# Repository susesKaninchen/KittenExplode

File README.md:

# KittenExplode
Das Projekt besteht aus einem I2C MAster und einer Reihe von I2C Slaves.

Momentan ist es auf ESP32 ausgelegt, diese haben kein I2C stretching und deswegen verhalten sie sich anders als ESP32 C3 oder STM32 oder Arduinos. Der Slave code müste dann angepasst werden.

Der Slave kann das Status Byte (statusChar) anpassen um dem Master bescheid zu geben wie der aktuelle Status ist.
Der Master kann das EndByte (endByte) anpassen um den Slaves den Stand des Spiel mitzuteilen.
Der vom Master gesetzte Seed (seed) soll genutzt werden um die Slaves zu konfigurieren.

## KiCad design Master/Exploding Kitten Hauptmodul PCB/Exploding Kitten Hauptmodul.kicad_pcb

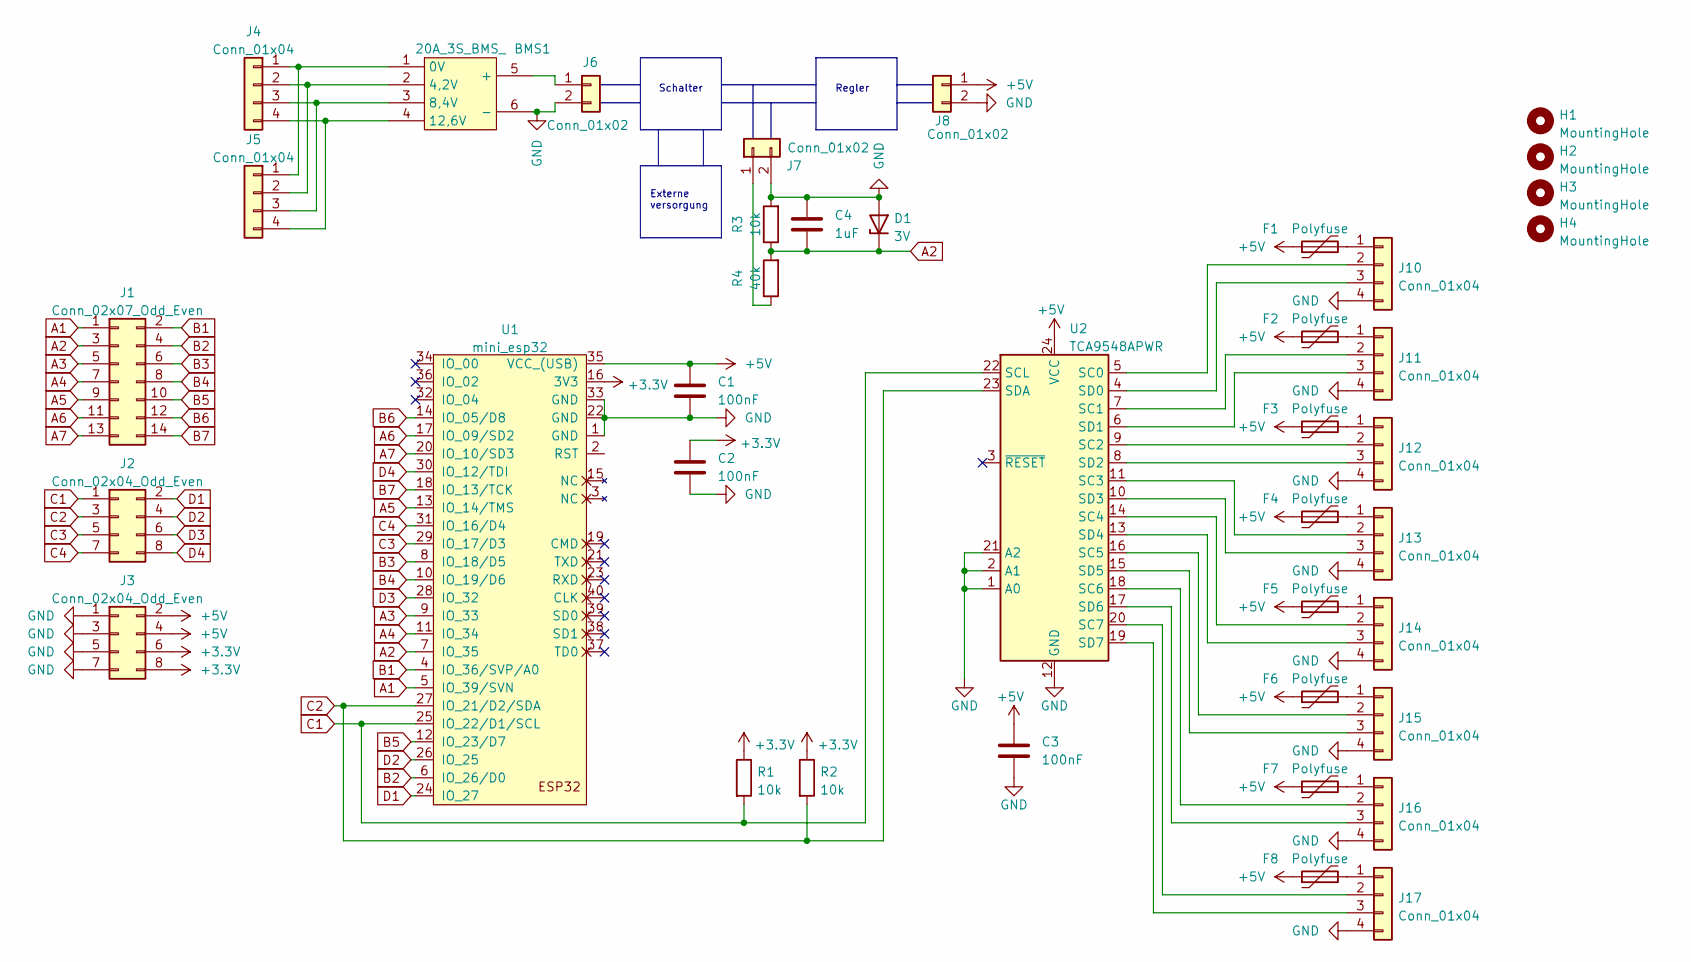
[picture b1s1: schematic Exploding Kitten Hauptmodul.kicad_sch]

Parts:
BMS1: 20A_3S_BMS_; 3S 20A BMS
C1, C2, C3: 100nF; C_0805_2012Metric
C4: 1uF; C_0805_2012Metric
D1: 3V; D_DO-41_SOD81_P7.62mm_Horizontal
F1, F2, F3, F4, F5, F6, F7, F8: Polyfuse; R_0805_2012Metric_Pad1.20x1.40mm_HandSolder
H1, H2, H3, H4: MountingHole; MountingHole_3.2mm_M3
J1: Conn_02x07_Odd_Even; PinHeader_2x07_P2.54mm_Vertical
J2, J3: Conn_02x04_Odd_Even; PinHeader_2x04_P2.54mm_Vertical
J4, J5, J10, J11, J12, J13, J14, J15, J16, J17: Conn_01x04; JST_EH_S4B-EH_1x04_P2.50mm_Horizontal
J6, J7, J8: Conn_01x02; TerminalBlock_bornier-2_P5.08mm
R1, R2, R3: 10k; R_0805_2012Metric
R4: 40k; R_0805_2012Metric
U1: mini_esp32; ESP32_mini
U2: TCA9548APWR; TSSOP-24_4.4x7.8mm_P0.65mm

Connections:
+3.3V: C2.1, J3.6, J3.8, R1.1, R2.1, U1.16 (3V3)
+5V: C1.1, C3.1, F1.1, F2.1, F3.1, F4.1, F5.1, F6.1, F7.1, F8.1, J3.2, J3.4, J8.1, U1.35 (VCC_(USB)), U2.24 (VCC)
A1: J1.1, U1.5 (IO_39/SVN)
A2: C4.2, D1.1 (K), J1.3, R3.1, R4.2, U1.7 (IO_35)
A3: J1.5, U1.9 (IO_33)
A4: J1.7, U1.11 (IO_34)
A5: J1.9, U1.13 (IO_14/TMS)
A6: J1.11, U1.17 (IO_09/SD2)
A7: J1.13, U1.20 (IO_10/SD3)
B1: J1.2, U1.4 (IO_36/SVP/A0)
B2: J1.4, U1.6 (IO_26/D0)
B3: J1.6, U1.8 (IO_18/D5)
B4: J1.8, U1.10 (IO_19/D6)
B5: J1.10, U1.12 (IO_23/D7)
B6: J1.12, U1.14 (IO_05/D8)
B7: J1.14, U1.18 (IO_13/TCK)
C1: J2.1, R1.2, U1.25 (IO_22/D1/SCL), U2.22 (SCL)
C2: J2.3, R2.2, U1.27 (IO_21/D2/SDA), U2.23 (SDA)
C3: J2.5, U1.29 (IO_17/D3)
C4: J2.7, U1.31 (IO_16/D4)
D1: J2.2, U1.24 (IO_27)
D2: J2.4, U1.26 (IO_25)
D3: J2.6, U1.28 (IO_32)
D4: J2.8, U1.30 (IO_12/TDI)
unnamed: BMS1.5 (+), J6.1
unnamed: F1.2, J10.1
unnamed: F2.2, J11.1
unnamed: F3.2, J12.1
unnamed: F4.2, J13.1
unnamed: F5.2, J14.1
unnamed: F6.2, J15.1
unnamed: F7.2, J16.1
unnamed: F8.2, J17.1
unnamed: BMS1.1 (0V), J4.1, J5.1
unnamed: BMS1.2 (4,2V), J4.2, J5.2
unnamed: BMS1.3 (8,4V), J4.3, J5.3
unnamed: BMS1.4 (12,6V), J4.4, J5.4
unnamed: J10.2, U2.5 (SC0)
unnamed: J10.3, U2.4 (SD0)
unnamed: J11.2, U2.7 (SC1)
unnamed: J11.3, U2.6 (SD1)
unnamed: J12.2, U2.9 (SC2)
unnamed: J12.3, U2.8 (SD2)
unnamed: J13.2, U2.11 (SC3)
unnamed: J13.3, U2.10 (SD3)
unnamed: J14.2, U2.14 (SC4)
unnamed: J14.3, U2.13 (SD4)
unnamed: J15.2, U2.16 (SC5)
unnamed: J15.3, U2.15 (SD5)
unnamed: J16.2, U2.18 (SC6)
unnamed: J16.3, U2.17 (SD6)
unnamed: J17.2, U2.20 (SC7)
unnamed: J17.3, U2.19 (SD7)
unnamed: J7.1, R4.1

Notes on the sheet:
Schalter
Externe versorgung
Regler

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
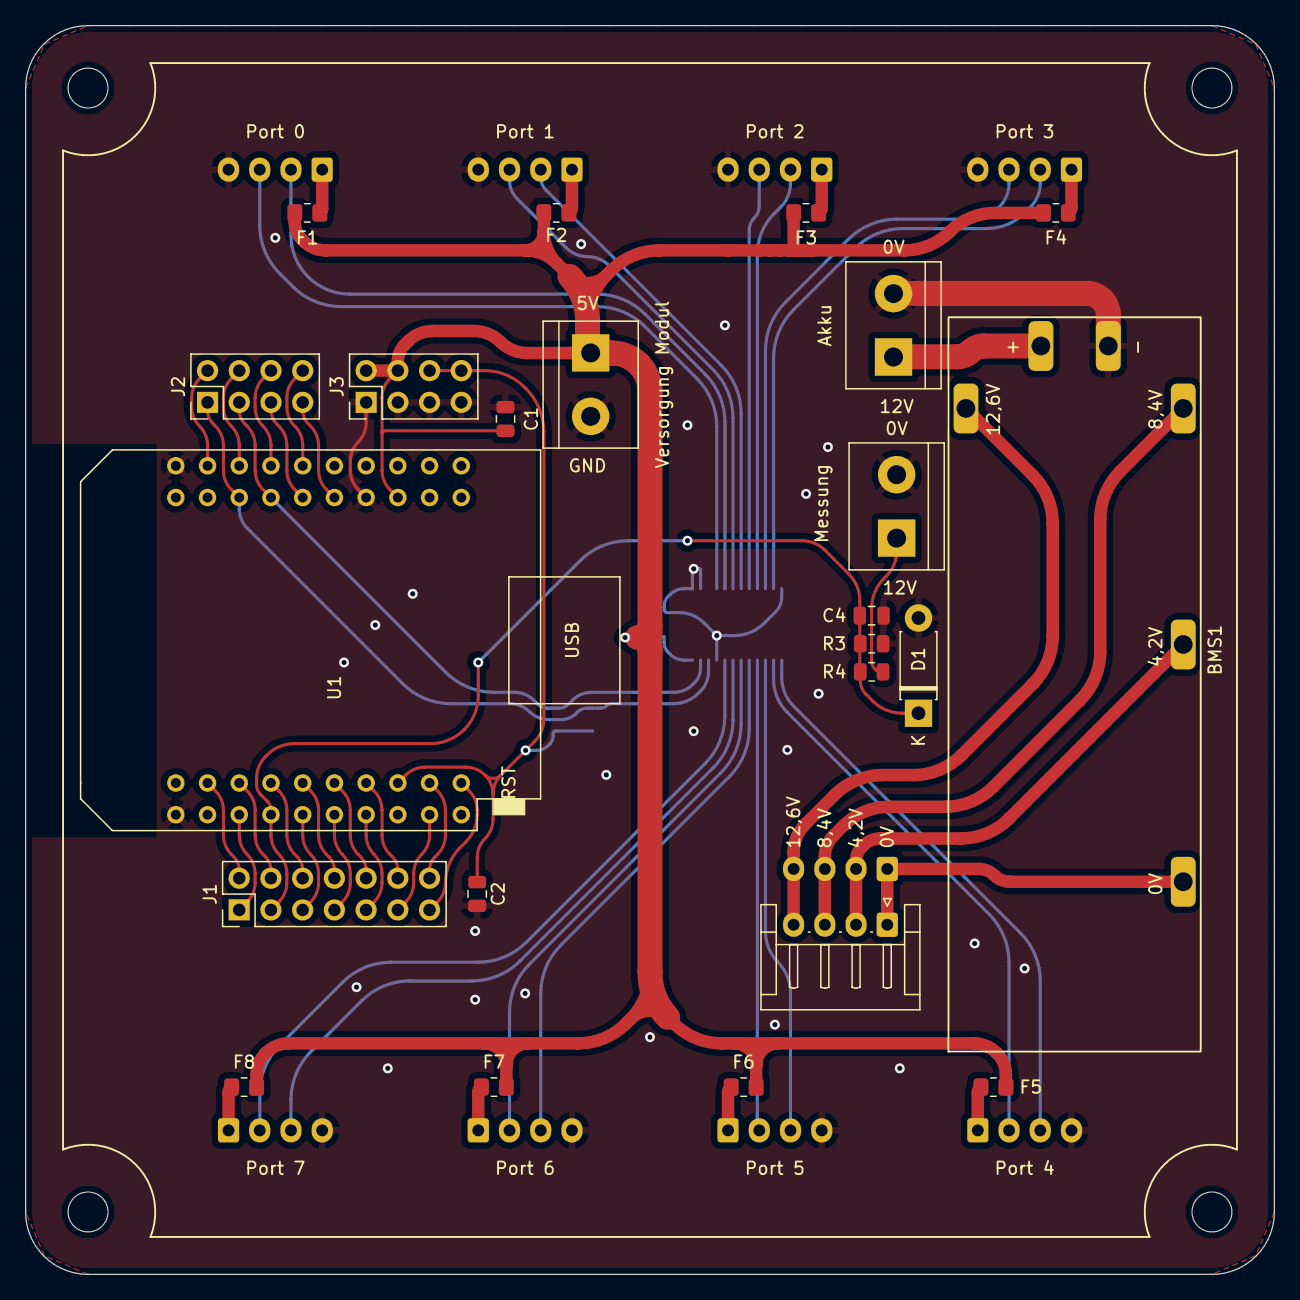
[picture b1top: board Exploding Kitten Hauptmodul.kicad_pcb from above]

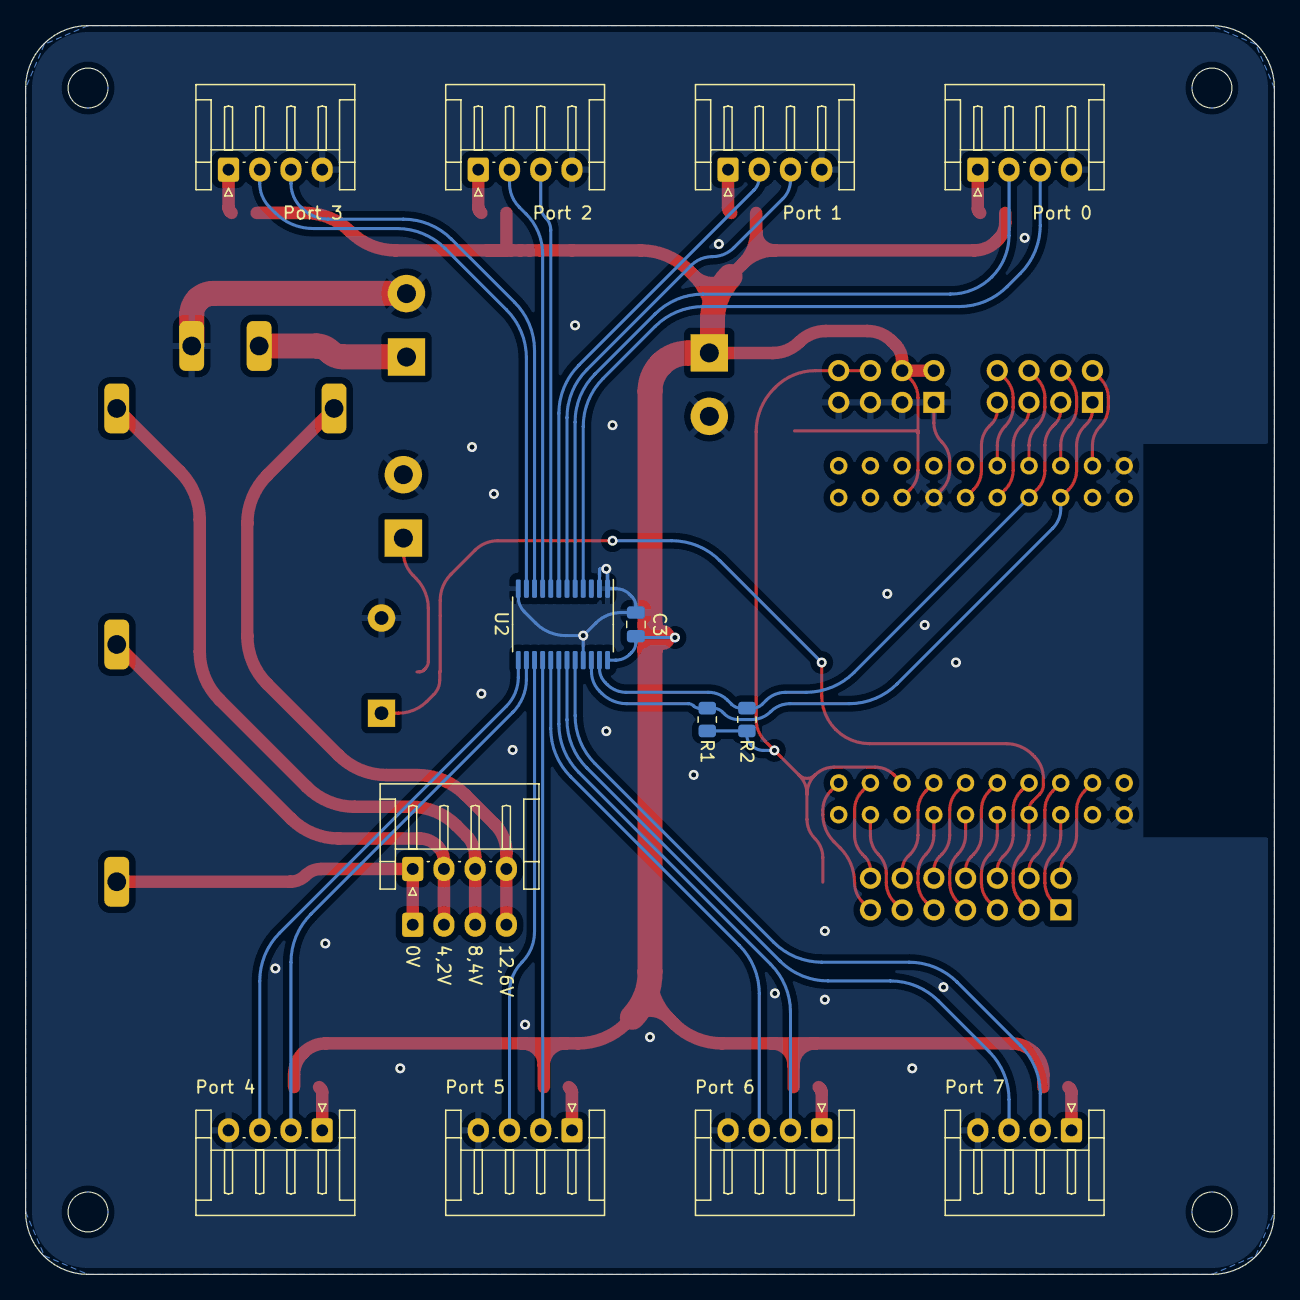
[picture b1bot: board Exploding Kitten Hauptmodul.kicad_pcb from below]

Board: 2 copper layers, 100.0 x 100.0 mm, 40 parts (13 on the bottom side), 55 nets.

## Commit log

2023-03-01 Initial Project
2023-03-03 Info
2023-03-03 Master PCB
2023-03-03 Web korrektur
2023-03-03 Segment und NeoPixel
2023-03-03 leds
2023-03-03 make platformio great again
2023-03-03 change to correct devboard
2023-03-04 more platformio changes
2023-03-04 fix neopixel pin
2023-03-04 fix slave i2c connection as client
2023-03-04 Master V0
2023-03-05 Add mod
2023-03-08 RandomShit Demo
2023-03-08 3D Dateien hinzugefügt
2023-03-08 kleine änderungen
2023-03-10 umbau auf timer
2023-03-11 Motorstromerkennung eingebaut
2023-03-12 Nur in Funktionen unterteielt
2023-03-12 SPI MAster communication + Win/Lost Animation
2023-03-12 segment
2023-03-13 Button Game implementiert
2023-06-24 Sahra
